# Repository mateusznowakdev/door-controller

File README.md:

Project description can be found on
[my website](https://mateusznowak.dev/projects/automatic-door-controller/).

User manual can be found in [docs](./docs/README.md) directory.

## Installing

(instructions for Linux)

1. Clone the repository.
    - `git clone --recurse-submodules https://github.com/mateusznowakdev/door-controller`
2. Download and flash CircuitPython 9.1.3 using the official instructions.
    - [Download](https://adafruit-circuit-python.s3.amazonaws.com/bin/raspberry_pi_pico/en_US/adafruit-circuitpython-raspberry_pi_pico-en_US-9.1.3.uf2)
3. Download mpy-cross binary to the `firmware` directory, rename it and make it
   executable.
    - [Download (amd64)](https://adafruit-circuit-python.s3.amazonaws.com/bin/mpy-cross/linux-amd64/mpy-cross-linux-amd64-9.1.3.static)
4. Build and upload the code to the CIRCUITPY drive
    - `cd firmware`
    - `./upload.sh`

## Language options

Can be changed by creating `settings.toml` file on the CIRCUITPY drive, with the
following content:

```toml
LANG = "pl"
```

Supported languages: `en`, `pl`

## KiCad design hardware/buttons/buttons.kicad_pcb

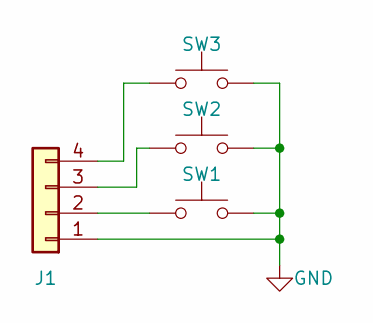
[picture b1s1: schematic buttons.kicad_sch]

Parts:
J1: Conn_01x04; PinSocket_1x04_P2.54mm_Vertical
SW1, SW2, SW3: SW_Push; SW_PUSH-12mm

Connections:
GND: J1.1, SW1.2, SW2.2, SW3.2
unnamed: J1.2, SW1.1
unnamed: J1.3, SW2.1
unnamed: J1.4, SW3.1

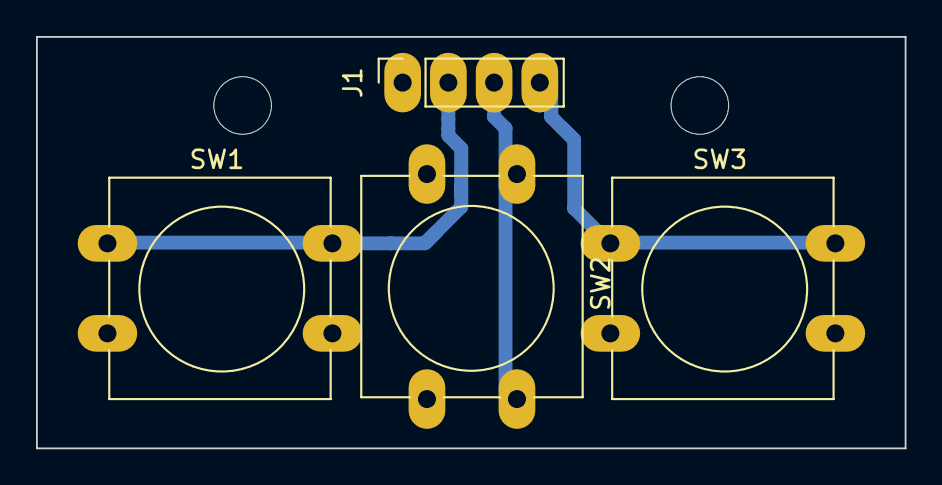
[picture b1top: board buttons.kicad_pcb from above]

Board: 2 copper layers, 48.3 x 22.9 mm, 4 parts (0 on the bottom side), 4 nets.

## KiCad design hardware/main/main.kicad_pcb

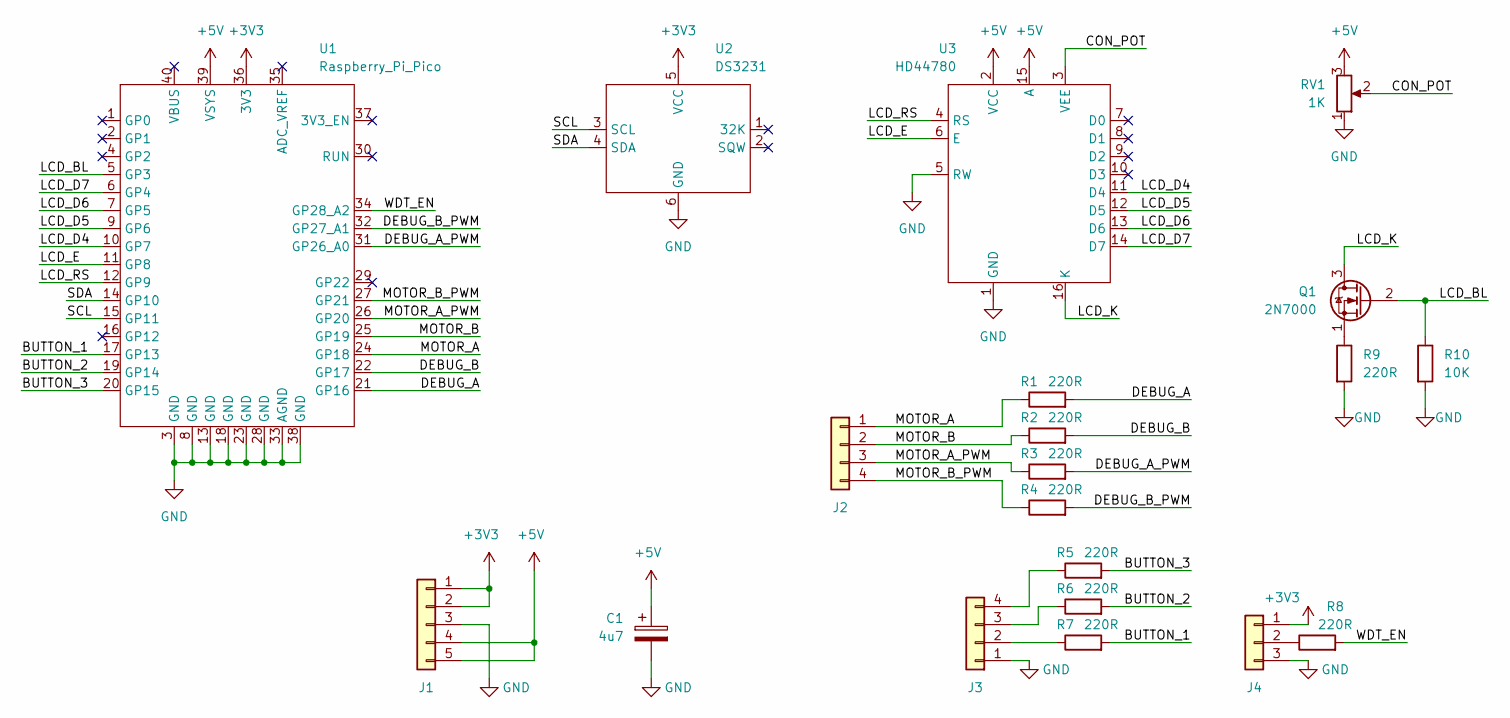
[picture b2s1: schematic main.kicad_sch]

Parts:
C1: 4u7; CP_Radial_D5.0mm_P2.50mm
J1: Conn_01x05; PinHeader_1x05_P2.54mm_Vertical
J2, J3: Conn_01x04; PinHeader_1x04_P2.54mm_Vertical
J4: Conn_01x03; PinHeader_1x03_P2.54mm_Vertical
Q1: 2N7000; TO-92_Inline_Wide
R1, R2, R3, R4, R5, R6, R7, R8, R9: 220R; R_Axial_DIN0207_L6.3mm_D2.5mm_P7.62mm_Horizontal
R10: 10K; R_Axial_DIN0207_L6.3mm_D2.5mm_P7.62mm_Horizontal
RV1: 1K; Potentiometer_Runtron_RM-065_Vertical
U1: Raspberry_Pi_Pico
U2: DS3231
U3: HD44780

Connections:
+3V3: J1.1, J1.2, J4.1, U1.36 (3V3), U2.5 (VCC)
+5V: C1.1, J1.4, J1.5, RV1.3, U1.39 (VSYS), U3.2 (VCC), U3.15 (A)
/BUTTON_1: R7.2, U1.17 (GP13)
/BUTTON_2: R6.2, U1.19 (GP14)
/BUTTON_3: R5.2, U1.20 (GP15)
/CON_POT: RV1.2, U3.3 (VEE)
/DEBUG_A: R1.2, U1.21 (GP16)
/DEBUG_A_PWM: R3.2, U1.31 (GP26_A0)
/DEBUG_B: R2.2, U1.22 (GP17)
/DEBUG_B_PWM: R4.2, U1.32 (GP27_A1)
/LCD_BL: Q1.2 (G), R10.1, U1.5 (GP3)
/LCD_D4: U1.10 (GP7), U3.11 (D4)
/LCD_D5: U1.9 (GP6), U3.12 (D5)
/LCD_D6: U1.7 (GP5), U3.13 (D6)
/LCD_D7: U1.6 (GP4), U3.14 (D7)
/LCD_E: U1.11 (GP8), U3.6 (E)
/LCD_K: Q1.3 (D), U3.16 (K)
/LCD_RS: U1.12 (GP9), U3.4 (RS)
/MOTOR_A: J2.1, R1.1, U1.24 (GP18)
/MOTOR_A_PWM: J2.3, R3.1, U1.26 (GP20)
/MOTOR_B: J2.2, R2.1, U1.25 (GP19)
/MOTOR_B_PWM: J2.4, R4.1, U1.27 (GP21)
/SCL: U1.15 (GP11), U2.3 (SCL)
/SDA: U1.14 (GP10), U2.4 (SDA)
/WDT_EN: R8.2, U1.34 (GP28_A2)
GND: C1.2, J1.3, J3.1, J4.3, R9.2, R10.2, RV1.1, U1.3 (GND), U1.8 (GND), U1.13 (GND), U1.18 (GND), U1.23 (GND), U1.28 (GND), U1.33 (AGND), U1.38 (GND), U2.6 (GND), U3.1 (GND), U3.5 (RW)
unnamed: J3.2, R7.1
unnamed: J3.3, R6.1
unnamed: J3.4, R5.1
unnamed: J4.2, R8.1
unnamed: Q1.1 (S), R9.1

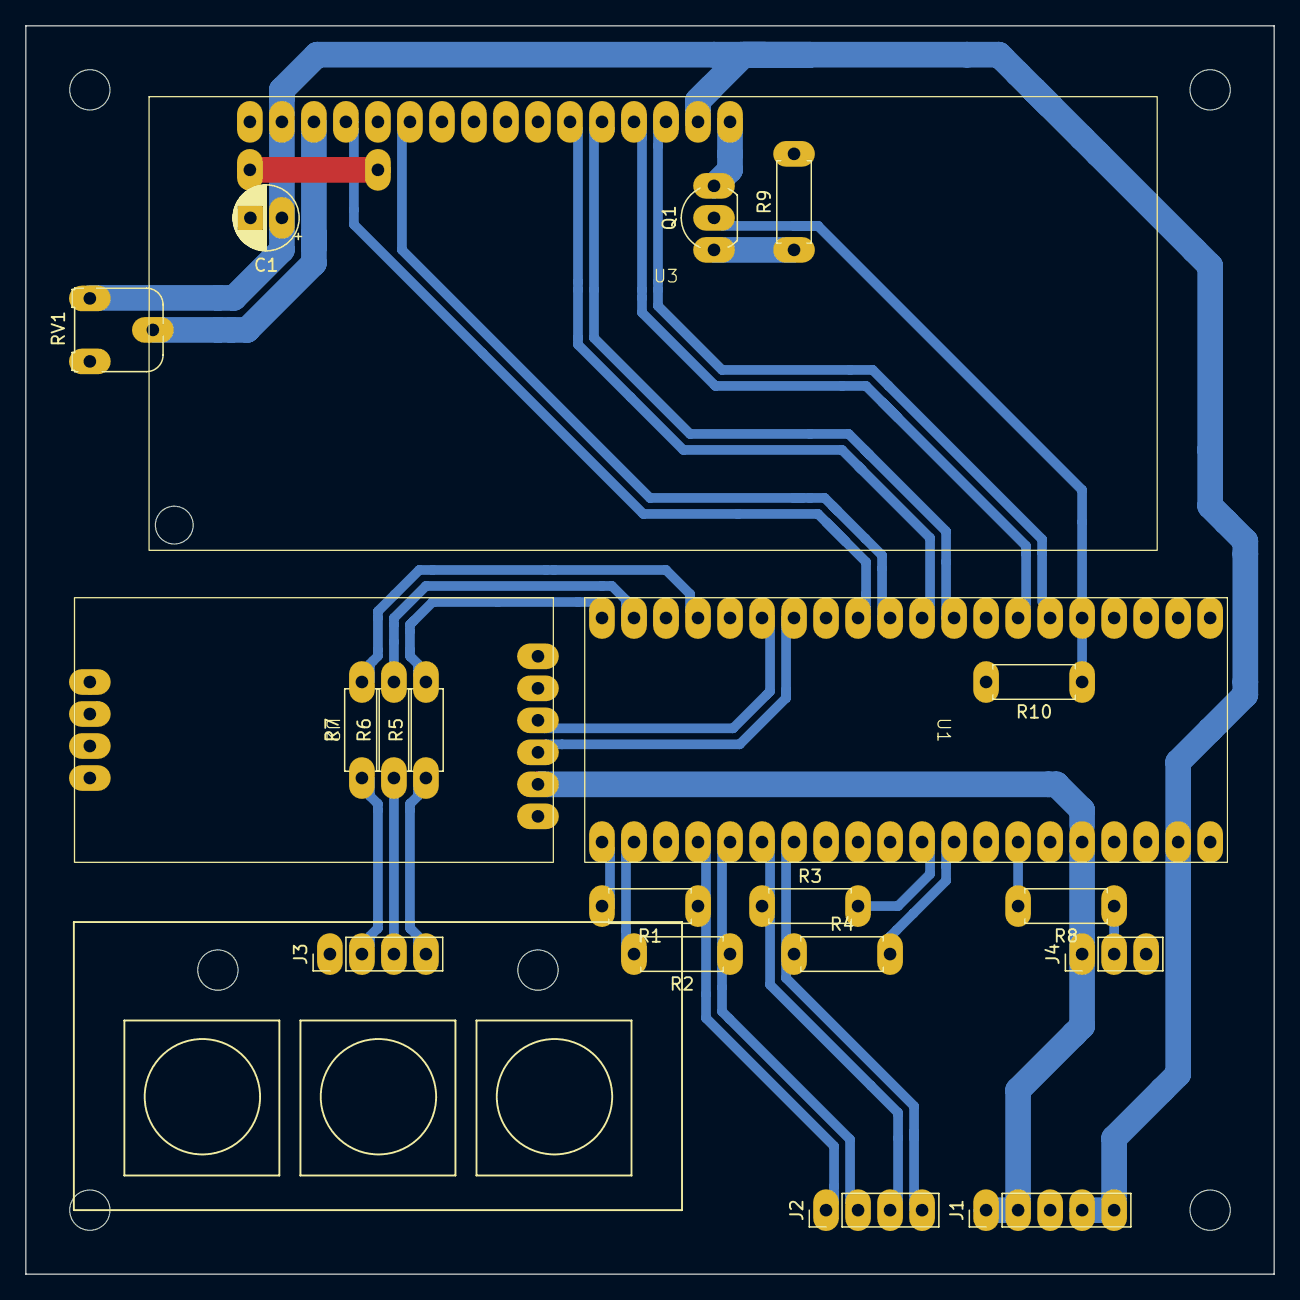
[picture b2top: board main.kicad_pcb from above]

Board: 2 copper layers, 99.1 x 99.1 mm, 20 parts (0 on the bottom side), 31 nets.

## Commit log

2024-01-06 Store board init log entry in the EEPROM
2024-01-06 Set maximum possible measured value
2024-01-06 Change cursor and backlight value on settings screen
2024-01-06 Handle end time being too close to start time
2024-01-06 Encapsulate display code
2024-01-06 Translate log entries
2024-01-06 Change RTC module time
2024-01-06 Include time tuple generator in the application code
2024-01-06 Refactor settings and scheduler code
2024-01-06 Convert menu loop to a coroutine
2024-01-06 Rename models to suggest only their instances should be used
2024-01-06 Display message if time is not valid
2024-01-06 Encapsulate menu cursor position and split key event handler
2024-01-06 Add basic logger
2024-01-06 Build mpy file and create dummy code.py file
2024-01-06 Update custom characters
2024-01-06 Refactor logging code
2024-01-06 Install dependencies in upload script's full mode
2024-01-06 Display current temperature
2024-01-06 Create own time formatting functions
2024-01-06 Handle end time being earlier than start time
2024-01-06 Return one-element list if divider is set to 1
2024-01-06 Split code into smaller files
2024-01-06 Add preview to the main menu
2024-01-06 Store data in buffer before sending to LCD
2024-01-06 Use rsync to copy files
2024-01-06 Refactor code
2024-01-06 Reduce number of modules
2024-01-06 Change menu icons
2024-01-06 Create event objects based on the schedule
2024-01-06 Update docs
2024-01-06 Use buttons to change cursor position
2024-01-06 Move enabling alternative icons to Menu.enter()
2024-01-06 Write message ID to EEPROM
2024-01-06 Create simple instruction manual based on existing features
2024-01-06 Refactor code to reduce nested ifs
2024-01-06 Check CircuitPython version before upload
2024-01-06 Set minimal LCD brightness when idle
2024-01-06 Display mocked opening setting values
2024-01-06 Move offset strings generation to menu.py
2024-01-06 Hide event log entry from main menu
2024-01-06 Display icon for opening and closing actions in preview menu
2024-01-06 Reset to factory settings if header mismatched
2024-01-06 Change values on the settings screen
2024-01-06 Add opening settings submenu
2024-01-06 Add closing settings menu and closing preview
2024-01-06 Do not re-upload unchanged files by default
2024-01-06 Create logging module
2024-01-06 Add separate log IDs for auto, manual and measure motor actions
2024-01-06 Store current time in a log entry
2024-01-06 Remove RTC class and use RTC module as a time source
2024-01-06 Rename code.py to main.py
2024-01-06 Choose which keys can be held
2024-01-06 Rename variables in get_time_tuples()
2024-01-06 Install code quality check tools
2024-01-06 Display scheduled times in the preview menu
2024-01-06 Stop motor if parent has cancelled the async task
2024-01-06 Move gettext to shared module
2024-01-06 Move firmware files to subdirectory
2024-01-06 Switch between two menu screens
2024-01-06 Add boot.py and safemode.py files
2024-01-06 Display text instead of log ID
2024-01-06 Add expected values for remaining tests
2024-01-06 Encapsulate keys code
2024-01-06 Display longer log messages
2024-01-06 Update user manual
2024-01-06 Add user menu translations
2024-01-06 Display log ID and time
2024-01-06 Rename shared module
2024-01-06 Update README once again
2024-01-06 Fix invalid action IDs
2024-01-06 Add auto-measurement menu
2024-01-06 Add watchdog and feed it in the scheduler loop
2024-01-06 Encapsulate switching between edit and navigation modes
2024-01-06 Create test cases for scheduler
2024-01-06 Add logging for auto-measurement
2024-01-06 Explicitly define pull mode for watchdog pin
2024-01-06 Show text on the LCD
2024-01-06 Encapsulate getting duration of single operation
2024-01-06 Add code for real motor driver
2024-01-06 Clean up rendering in setting menus
2024-01-06 Encapsulate main menu
2024-01-06 Detect location of the last log entry
2024-01-06 Refactor code, add type hints and constants
2024-01-06 Transform logging module into constants module
2024-01-06 Add more custom icons
2024-01-06 Move types to separate module
2024-01-06 Restore settings reset function
2024-01-06 Make sure events have execution timestamp in the future
2024-01-06 Remove redundant field from HistoryT
2024-01-06 Create time offsets instead of time tuples, for preview purposes
2024-01-06 Change layout of preview and log screens
2024-01-06 Do not send text to the LCD if buffer content has not changed
2024-01-06 Add KiCAD files to .gitignore
2024-01-06 Store and verify data checksum
2024-01-06 Add history menu and show raw data
2024-01-06 Reset max EEPROM size to the default value
2024-01-06 Add asynchronous motor functions
2024-01-06 Restart scheduler on settings/time change
2024-01-06 Create new project
2024-01-06 Change LCD backlight value
2024-01-06 Require key to be held to enter the menu
2024-01-06 Do not store some logs in the EEPROM
2024-01-06 Change content displayed on opening settings menu
2024-01-06 Return empty list if duration is set to 0
2024-01-06 Run scheduler tasks
2024-01-06 Add initial README
2024-01-06 Add hardware files
2024-01-06 Add __pycache__ to .gitignore
2024-01-06 Add seconds in system time menu
2024-01-06 Remove mpy files after upload
2024-01-06 Display time preview
2024-01-06 Display watchdog status on the idle screen
2024-01-06 Rename occurrences of 'forward' and 'backward' in motor code
2024-01-06 Get and display time from RTC module
2024-01-06 Return to first available EEPROM address when necessary
2024-01-06 Create fake motor class
2024-01-06 Prevent controlling motor from multiple sources at the same time
2024-01-06 Use references to self instead of protected classes
2024-01-06 Add cancel button in setting menus
2024-01-06 Display current time on the idle screen
2024-01-06 Create valid times list for sample schedule
2024-01-06 Write message ID to subsequent EEPROM memory addresses
2024-01-06 Remove custom message for scheduler restart
2024-01-06 Change character set for some menus
2024-01-06 Restore some pylint rules and adapt the source code
2024-01-06 Change display brightness when switching menu screens
2024-01-06 Change layout of MeasurementMenu
2024-01-06 Change EEPROM data or system clock only if different from initial
2024-01-06 Change naming conventions, re-use constants and clean up comments
2024-01-06 Remove redundant Motor.run() function
2024-01-06 Draw icons and create simple menu mockup
2024-01-06 Improve logging messages
2024-01-06 Create events for both opening and closing
2024-01-06 Extract constants from app.common
2024-01-06 Add hardware drawings
2024-01-06 Change base checksum value to avoid false negatives
2024-01-06 Do not generate .mpy output for test files
2024-01-06 Use consistent format of motor actions reason
2024-01-06 Hold down the key to change values faster
2024-01-06 Save data to and read from EEPROM
2024-01-06 Add empty README file
2024-04-12 Rename entrypoint file to code.py
2024-04-12 Add dependencies as submodules
2024-09-04 Define all pins in the beginning of core.py
2024-09-04 Change pinout for the second board
2024-09-04 Change motor config and hardcode non-integer durations
2024-09-04 Display up to 99 history entries
2024-09-04 Remove extra motor settings from the menu
2024-09-04 Patch new settings object to make sure there's only one action per day
2024-09-04 Fix invalid keys pins
2024-09-04 Remove text for unused features of motor menu
2024-09-04 Update libraries
